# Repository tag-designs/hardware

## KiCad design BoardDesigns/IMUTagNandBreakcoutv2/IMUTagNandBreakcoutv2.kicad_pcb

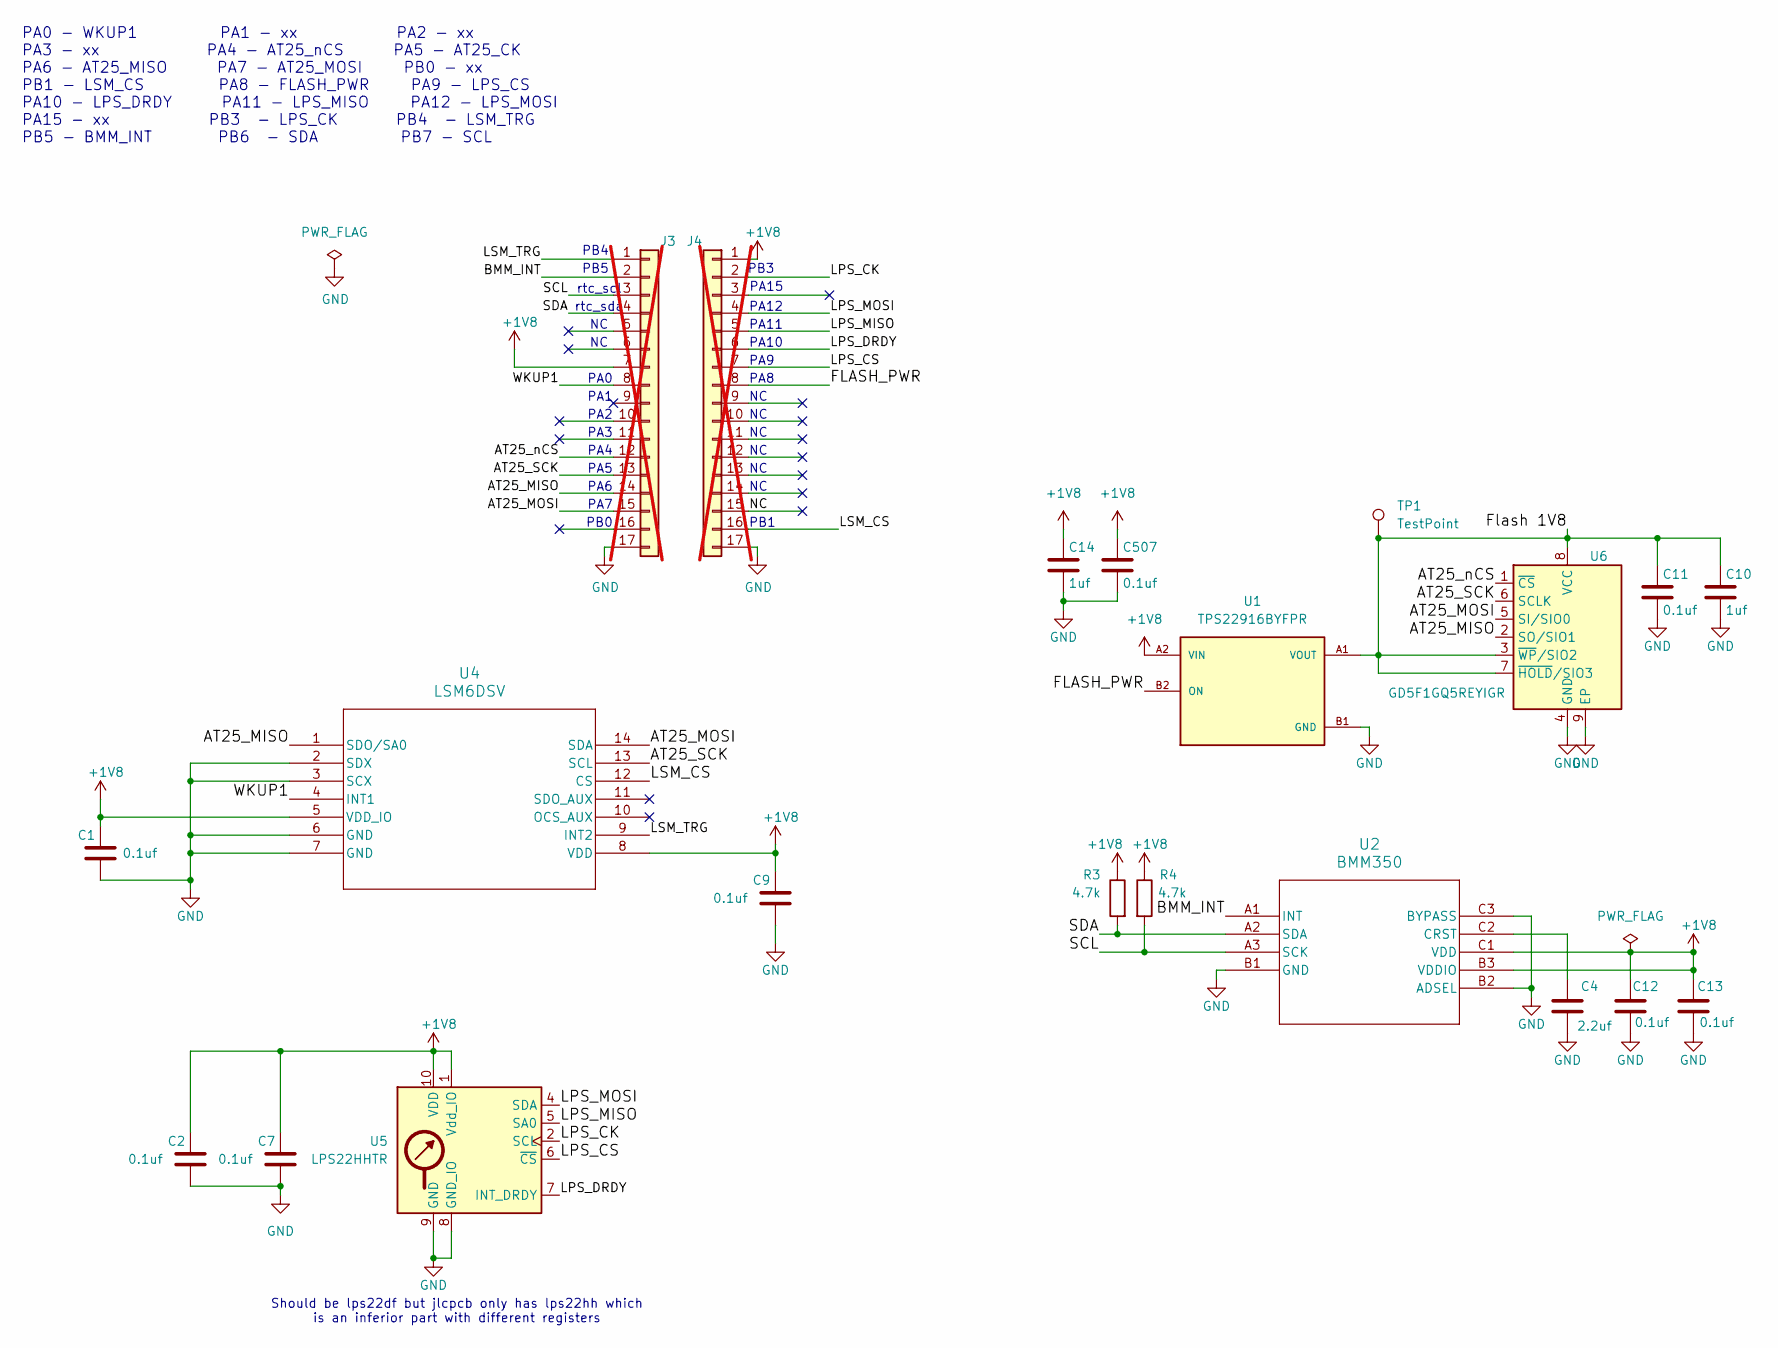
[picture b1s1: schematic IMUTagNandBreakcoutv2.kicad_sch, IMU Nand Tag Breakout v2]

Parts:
C1, C2, C7, C9, C11, C12, C13, C507: 0.1uf; C_0603_1608Metric; MPN CC0603KRX7R9BB104; LCSC C14663
C4: 2.2uf; C_0603_1608Metric; MPN GRM188R61H225KE11D; LCSC C162273
C10, C14: 1uf; C_0603_1608Metric; MPN CL10A105KB8NNNC; LCSC C15849
J3, J4: Conn_01x17; PinHeader_1x17_P2.54mm_Vertical_Staggered; not fitted
R3, R4: 4.7k; R_0603_1608Metric; MPN 0603WAF4701T5E; LCSC C23162
TP1: TestPoint; TestPoint_Pad_D2.0mm
U1: TPS22916BYFPR; IC_TPS22916BYFPR; PARTREV F; LCSC C2150095
U2: BMM350; BGA9_BMM350_BOS; MPN BMM350; LCSC C17225907
U4: LSM6DSV; LGA14-L_2P59X3P1X0P5_STM; MPN LSM6DSV; LCSC C5267399
U5: LPS22HHTR; ST_HLGA-10_2x2mm_P0.5mm_LayoutBorder3x2y; MPN LPS22HHTR; LCSC C2827824
U6: GD5F1GQ5REYIGR; WSON-8-1EP_8x6mm_P1.27mm_EP3.4x4.3mm; MPN GD5F1GQ5REYIGR; LCSC C2927042

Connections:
+1V8: C1.1, C2.1, C7.1, C9.1, C12.1, C13.1, C14.1, C507.1, J3.7, J4.1, R3.1, R4.1, U1.A2 (VIN), U2.B3 (VDDIO), U2.C1 (VDD), U4.5 (VDD_IO), U4.8 (VDD), U5.1 (Vdd_IO), U5.10 (VDD)
/AT25_MISO: J3.14, U4.1 (SDO/SA0), U6.2 (SO/SIO1)
/AT25_MOSI: J3.15, U4.14 (SDA), U6.5 (SI/SIO0)
/AT25_SCK: J3.13, U4.13 (SCL), U6.6 (SCLK)
/AT25_nCS: J3.12, U6.1 (~CS)
/BMM_INT: J3.2, U2.A1 (INT)
/FLASH_PWR: J4.8, U1.B2 (ON)
/Flash 1V8: C10.1, C11.1, TP1.1 (1_1), U1.A1 (VOUT), U6.3 (~WP/SIO2), U6.7 (~HOLD/SIO3), U6.8 (VCC)
/LPS_CK: J4.2, U5.2 (SCL)
/LPS_CS: J4.7, U5.6 (~CS)
/LPS_DRDY: J4.6, U5.7 (INT_DRDY)
/LPS_MISO: J4.5, U5.5 (SA0)
/LPS_MOSI: J4.4, U5.4 (SDA)
/LSM_CS: J4.16, U4.12 (CS)
/LSM_TRG: J3.1, U4.9 (INT2)
/NC: J4.15
/SCL: J3.3, R4.2, U2.A3 (SCK)
/SDA: J3.4, R3.2, U2.A2 (SDA)
/WKUP1: J3.8, U4.4 (INT1)
GND: C1.2, C2.2, C4.2, C7.2, C9.2, C10.2, C11.2, C12.2, C13.2, C14.2, C507.2, J3.17, J4.17, U1.B1 (GND), U2.B1 (GND), U2.B2 (ADSEL), U2.C3 (BYPASS), U4.2 (SDX), U4.3 (SCX), U4.6 (GND), U4.7 (GND), U5.3 (GND), U5.8 (GND_IO), U5.9 (GND), U6.4 (GND), U6.9 (EP)
unnamed: C4.1, U2.C2 (CRST)

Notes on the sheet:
PA1
PA9
PA2
PA0
PA8
PA7
PA15
PA5
PA4
PB3
PA6
Should be lps22df but jlcpcb only has lps22hh which is an inferior part with different registers
PA3
PA0 - WKUP1 PA1 - xx PA2 - xx PA3 - xx PA4 - AT25_nCS PA5 - AT25_CK PA6 - AT25_MISO PA7 - AT25_MOSI PB0 - xx PB1 - LSM_CS PA8 - FLASH_PWR PA9 - LPS_CS PA10 - LPS_DRDY PA11 - LPS_MISO PA12 - LPS_MOSI PA15 - xx PB3 - LPS_CK PB4 - LSM_TRG PB5 - BMM_INT PB6 - SDA PB7 - SCL
PB4
PA12
PB0
PB5
PA10
rtc_sda
PA11
PB1
rtc_scl

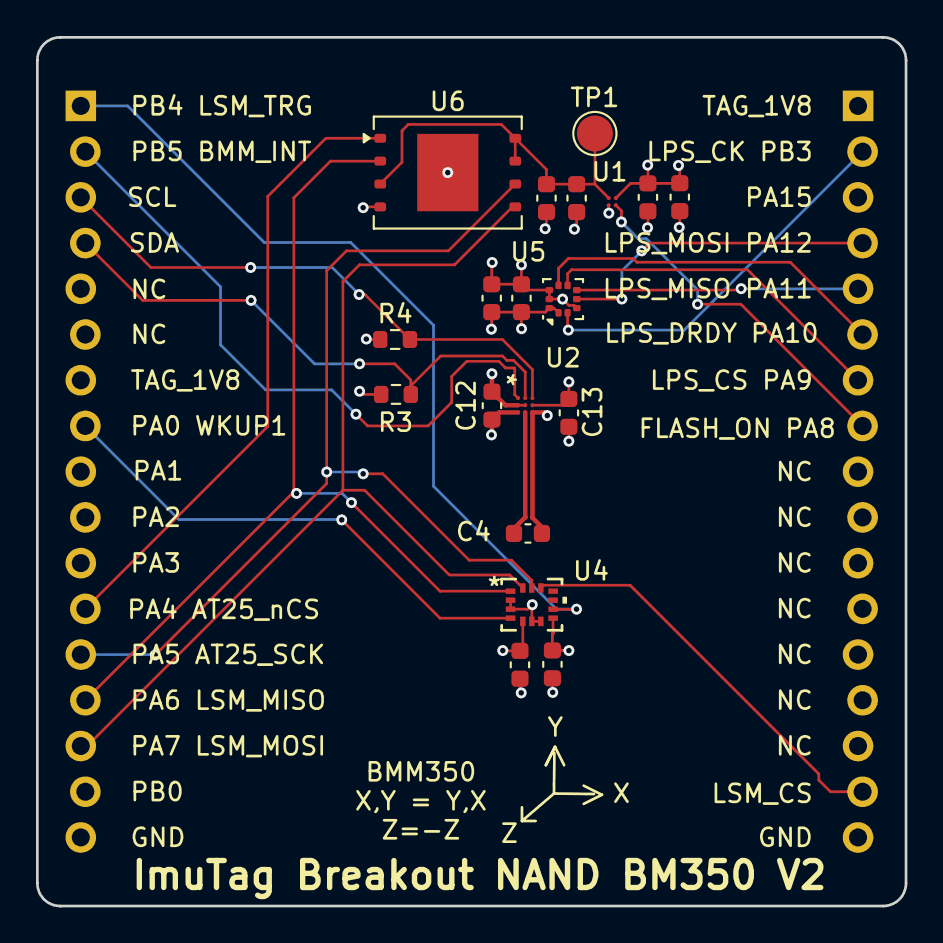
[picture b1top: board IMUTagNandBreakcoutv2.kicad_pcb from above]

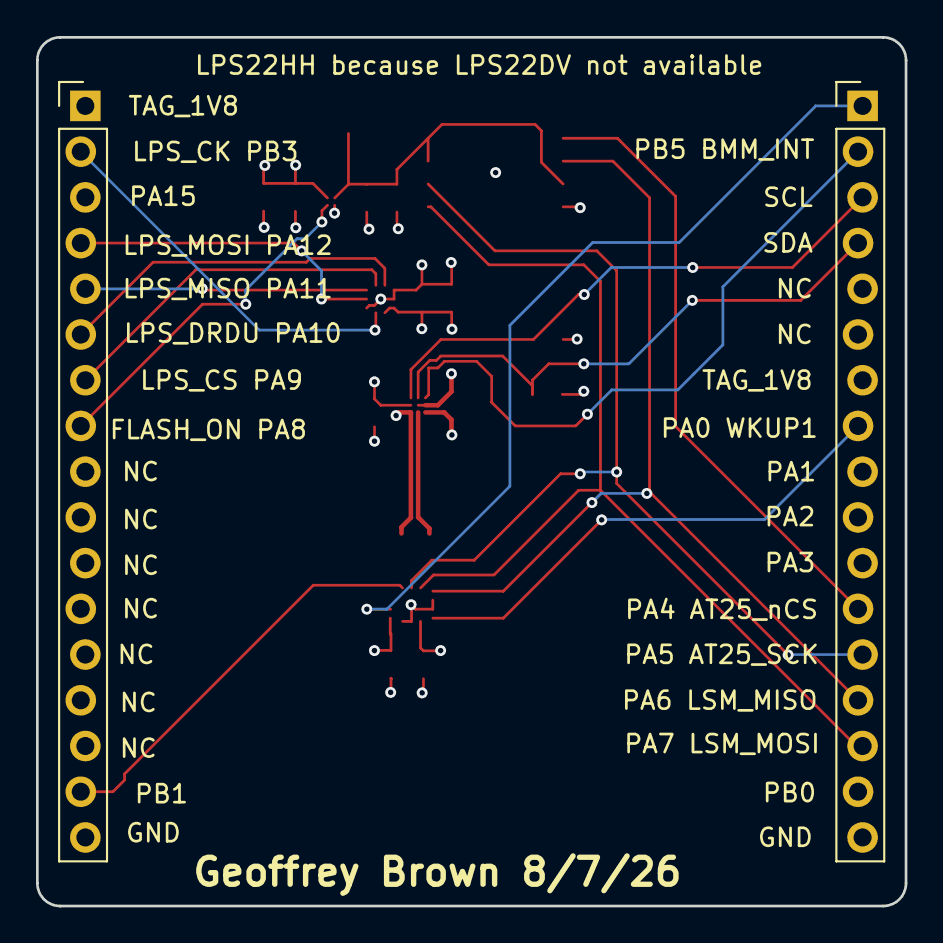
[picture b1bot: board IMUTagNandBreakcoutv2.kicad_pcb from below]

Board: 4 copper layers, 48.3 x 48.3 mm, 21 parts (2 on the bottom side), 20 nets.

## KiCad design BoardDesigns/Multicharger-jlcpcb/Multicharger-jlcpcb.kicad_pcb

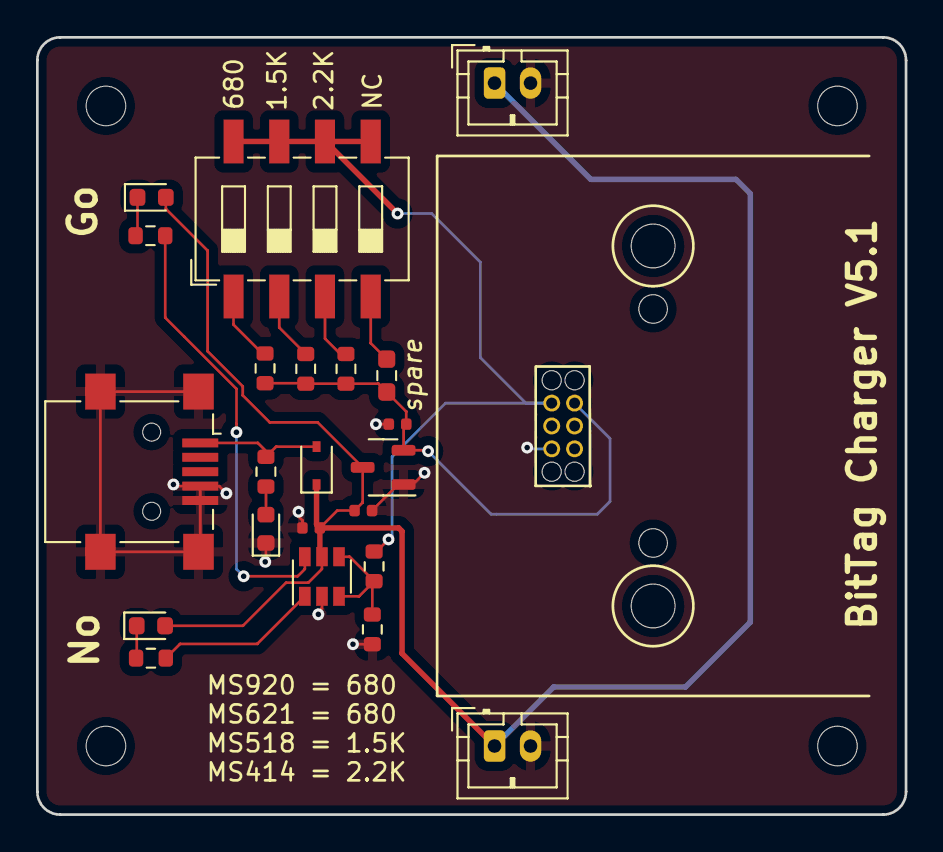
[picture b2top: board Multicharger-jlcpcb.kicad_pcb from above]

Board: 2 copper layers, 48.3 x 43.2 mm, 27 parts (0 on the bottom side), 15 nets.

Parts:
C101: 0.1uF; C_0402_1005Metric
C106: 1uF; C_0402_1005Metric
C107: 2.2uF; C_0402_1005Metric
D101: No Go Red; LED_0603_1608Metric
D102: BLUE; LED_0603_1608Metric
D103: Go Green; LED_0603_1608Metric
D104: D_Schottky; D_SOD-323
J101, J102: Conn_01x02; JST_PH_B2B-PH-K_1x02_P2.00mm_Vertical
J103: Tagbase; 6pin_tagpoints_new_offset
J104: USB_B_Mini; USB_Mini-B_Lumberg_2486_01_Horizontal
MK101, MK102, MK103, MK104: Mounting_Hole; MountingHole_2.2mm_M2
R1: 680; R_0603_1608Metric
R2: spare; R_0603_1608Metric_Pad0.98x0.95mm_HandSolder
R101: 330; R_0603_1608Metric
R102, R105: 220; R_0603_1608Metric
R103: 91K; R_0603_1608Metric
R104: 13K; R_0603_1608Metric
R106: 1500; R_0603_1608Metric
R107: 2.2K; R_0603_1608Metric
SW101: SW_DIP_x04; SW_DIP_SPSTx04_Slide_6.7x11.72mm_W8.61mm_P2.54mm_LowProfile
U101: TPS3700; SOT-23-6
U106: AP7370; SOT-23-3

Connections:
+3V3: C107.1, J103.5, R1.2, R2.1, R106.2, R107.2, U106.2 (VO)
/VIN: C101.1, C106.1, D101.2 (A), D103.2 (A), D104.1 (K), J101.1, J102.1, U101.5 (VDD), U106.3 (VI)
/Vsense: R103.2, R104.1, U101.3 (INA+), U101.4 (INB-)
GND: C101.2, C106.2, C107.2, D102.1 (K), J101.2, J102.2, J103.2, J104.4 (ID), J104.5 (GND), J104.6 (Shield), R104.2, U101.2 (GND), U106.1 (GND)
unnamed: D101.1 (K), R101.2
unnamed: D102.2 (A), R102.2
unnamed: D103.1 (K), R105.2
unnamed: D104.2 (A), J104.1 (VBUS), R102.1
unnamed: R1.1, SW101.1
unnamed: R2.2, SW101.4
unnamed: R101.1, U101.1 (OUTA)
unnamed: R105.1, U101.6 (OUTB)
unnamed: R106.1, SW101.2
unnamed: R107.1, SW101.3
TAG_VBAT: J103.6, R103.1, SW101.5, SW101.6, SW101.7, SW101.8

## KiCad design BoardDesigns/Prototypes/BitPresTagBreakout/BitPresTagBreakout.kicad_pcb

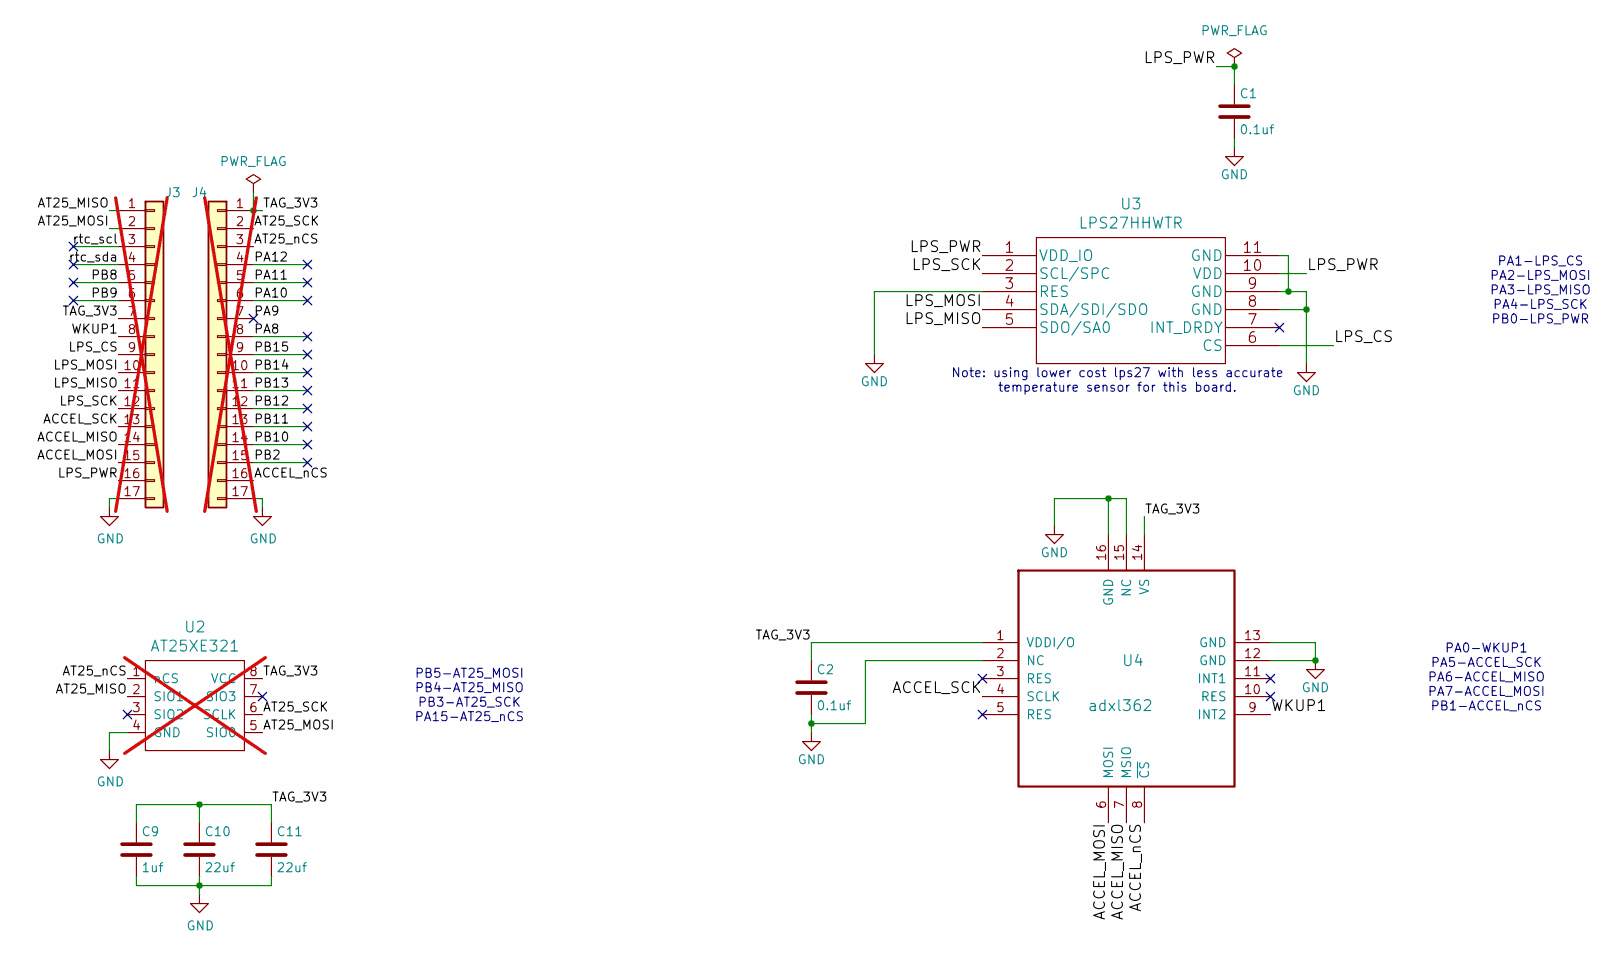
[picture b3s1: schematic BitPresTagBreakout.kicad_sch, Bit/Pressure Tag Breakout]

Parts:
C1, C2: 0.1uf; C_0201_0603Metric; MPN GRM033C81E104KE14D; LCSC C181047
C9: 1uf; C_0201_0603Metric; MPN GRM033R60J105MEA2D; LCSC C76930
C10, C11: 22uf; C_0402_1005Metric; MPN 04026D226MAT2A; LCSC C2179118
J3, J4: Conn_01x17; PinHeader_1x17_P2.54mm_Vertical_Staggered; not fitted
U2: AT25XE321; SO-8_5.3x6.2mm_P1.27mm; MPN AT25XE321D-SSHN-T; LCSC C7455379; not fitted
U3: LPS27HHWTR; MPN LPS27HHWTR; LCSC C3010792
U4: adxl362; ADXL362; MPN ADXL362BCCZ-RL7; LCSC C192252

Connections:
/ACCEL_MISO: J3.14, U4.7 (MSIO)
/ACCEL_MOSI: J3.15, U4.6 (MOSI)
/ACCEL_SCK: J3.13, U4.4 (SCLK)
/ACCEL_nCS: J4.16, U4.8 (~CS)
/AT25_MISO: J3.1, U2.2 (SIO1)
/AT25_MOSI: J3.2, U2.5 (SIO0)
/AT25_SCK: J4.2, U2.6 (SCLK)
/AT25_nCS: J4.3, U2.1 (nCS)
/LPS_CS: J3.9, U3.6 (CS)
/LPS_MISO: J3.11, U3.5 (SDO/SA0)
/LPS_MOSI: J3.10, U3.4 (SDA/SDI/SDO)
/LPS_PWR: C1.1, J3.16, U3.1 (VDD_IO), U3.10 (VDD)
/LPS_SCK: J3.12, U3.2 (SCL/SPC)
/PA8: J4.8
/PA9: J4.7
/PA10: J4.6
/PA11: J4.5
/PA12: J4.4
/PB2: J4.15
/PB8: J3.5
/PB9: J3.6
/PB10: J4.14
/PB11: J4.13
/PB12: J4.12
/PB13: J4.11
/PB14: J4.10
/PB15: J4.9
/TAG_3V3: C2.1, C9.1, C10.1, C11.1, J3.7, J4.1, U2.8 (VCC), U4.1 (VDDI/O), U4.14 (VS)
/WKUP1: J3.8, U4.9 (INT2)
/rtc_scl: J3.3
/rtc_sda: J3.4
GND: C1.2, C2.2, C9.2, C10.2, C11.2, J3.17, J4.17, U2.4 (GND), U3.3 (RES), U3.8 (GND), U3.9 (GND), U3.11 (GND), U4.2 (NC), U4.12 (GND), U4.13 (GND), U4.15 (NC), U4.16 (GND)

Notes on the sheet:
Note: using lower cost lps27 with less accurate temperature sensor for this board.
PA0-WKUP1 PA5-ACCEL_SCK PA6-ACCEL_MISO PA7-ACCEL_MOSI PB1-ACCEL_nCS
PA1-LPS_CS PA2-LPS_MOSI PA3-LPS_MISO PA4-LPS_SCK PB0-LPS_PWR
PB5-AT25_MOSI PB4-AT25_MISO PB3-AT25_SCK PA15-AT25_nCS

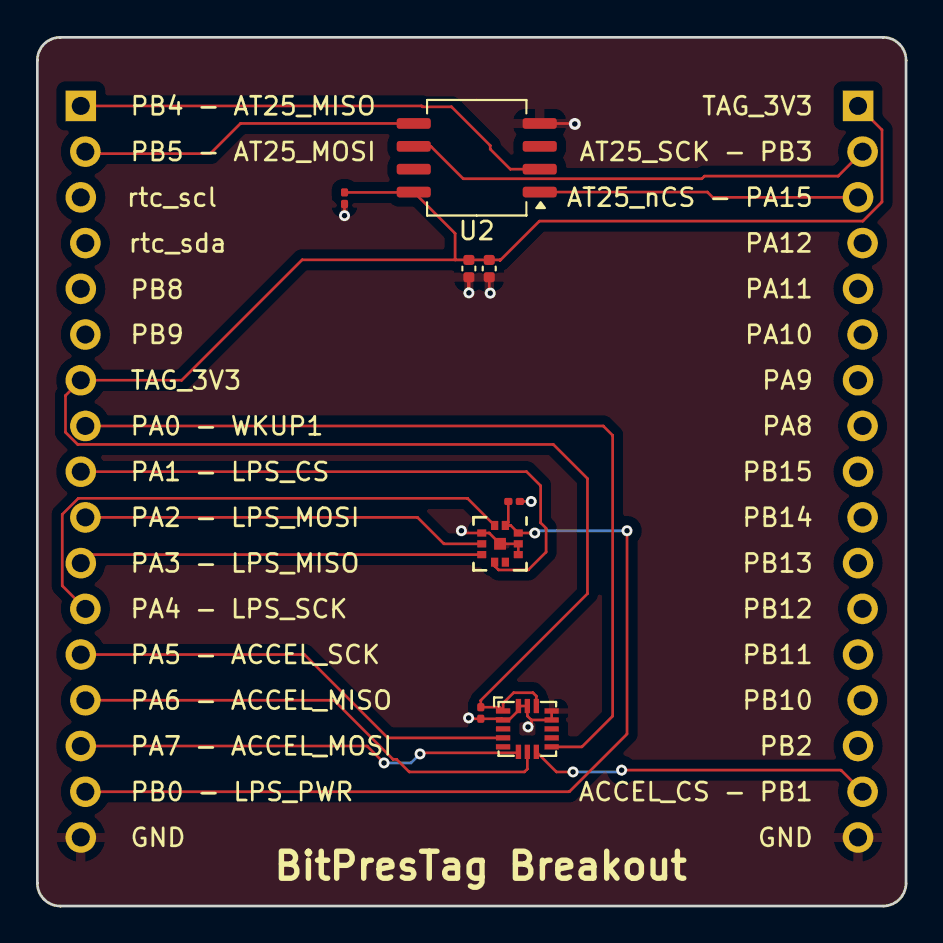
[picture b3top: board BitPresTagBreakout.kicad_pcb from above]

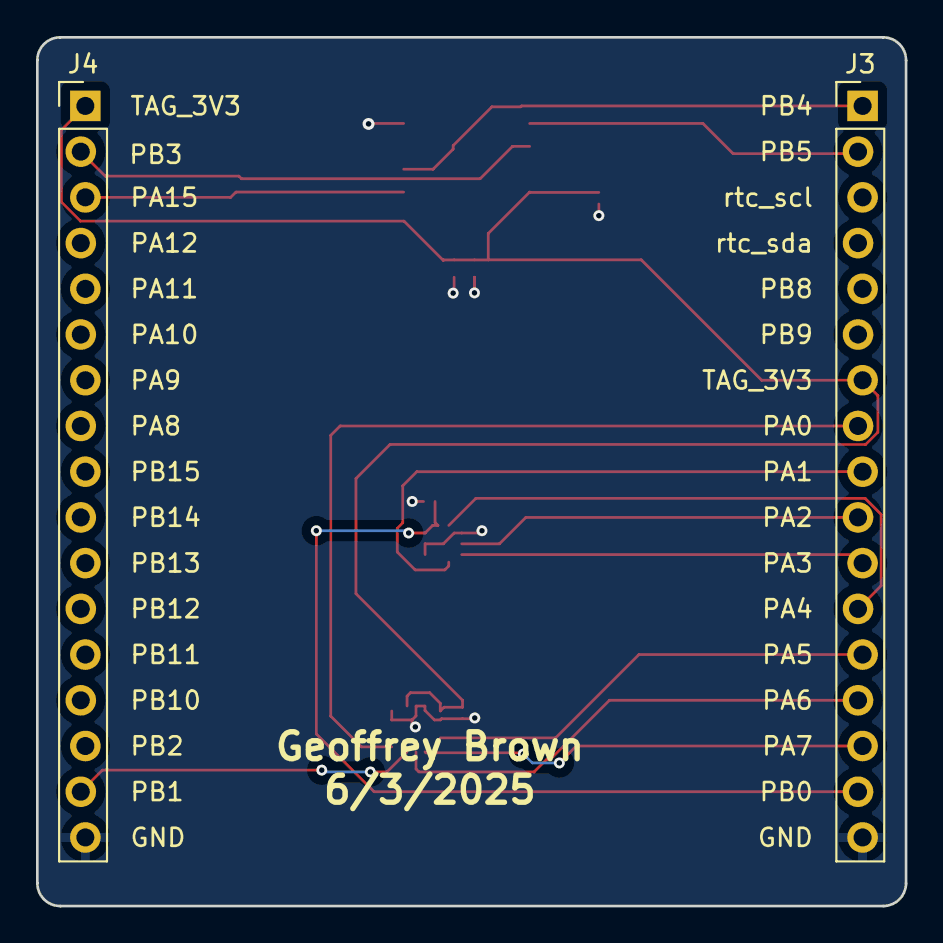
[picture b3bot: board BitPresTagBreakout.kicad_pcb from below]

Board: 2 copper layers, 48.3 x 48.3 mm, 10 parts (2 on the bottom side), 16 nets.

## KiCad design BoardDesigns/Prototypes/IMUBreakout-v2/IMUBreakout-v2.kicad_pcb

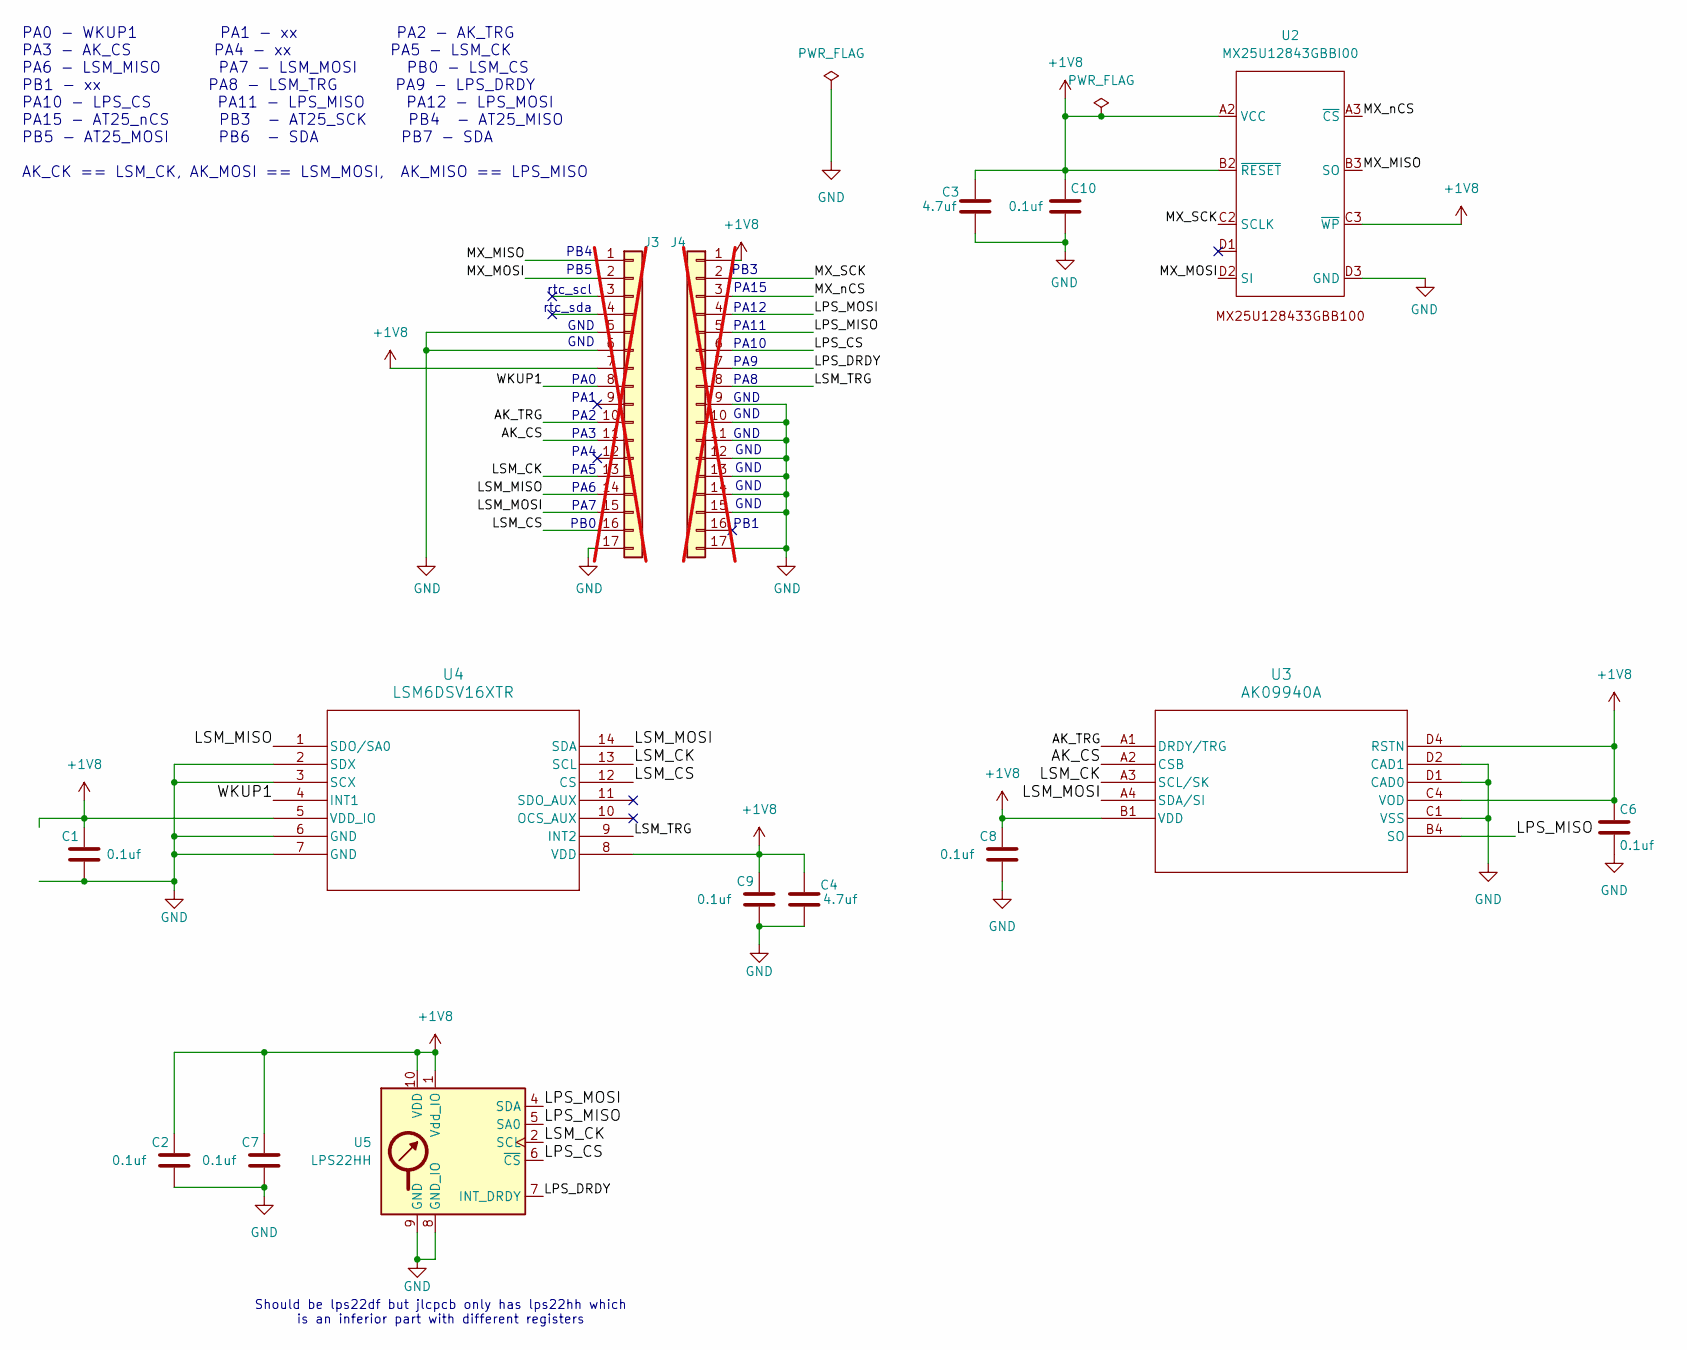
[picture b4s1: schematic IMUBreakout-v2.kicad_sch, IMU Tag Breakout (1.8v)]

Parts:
C1, C2, C6, C7, C8, C9, C10: 0.1uf; C_0603_1608Metric; MPN CC0603KRX7R9BB104; LCSC C14663
C3, C4: 4.7uf; C_0603_1608Metric; MPN CL10A475KO8NNNC; LCSC C19666
J3, J4: Conn_01x17; PinHeader_1x17_P2.54mm_Vertical_Staggered; not fitted
U2: MX25U12843GBBI00; IC_MX25U12843GBBI00; MPN MX25U12843GBBI00; LCSC C7316586
U3: AK09940A; AK09940a; MPN AK09940A; LCSC C6794828
U4: LSM6DSV16XTR; LGA-14_3x2.5mm_P0.5mm_LayoutBorder3x4y; MPN LSM6DSV; LCSC C5267406
U5: LPS22HH; ST_HLGA-10_2x2mm_P0.5mm_LayoutBorder3x2y; MPN LPS22HH; LCSC C2827824

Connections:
+1V8: C1.1, C2.1, C3.1, C4.1, C6.1, C7.1, C8.1, C9.1, C10.1, J3.7, J4.1, U2.A2 (VCC), U2.B2 (~RESET), U2.C3 (~WP), U3.B1 (VDD), U3.C4 (VOD), U3.D4 (RSTN), U4.5 (VDD_IO), U4.8 (VDD), U5.1 (Vdd_IO), U5.10 (VDD)
/AK_CS: J3.11, U3.A2 (CSB)
/AK_TRG: J3.10, U3.A1 (DRDY/TRG)
/LPS_CS: J4.6, U5.6 (~CS)
/LPS_DRDY: J4.7, U5.7 (INT_DRDY)
/LPS_MISO: J4.5, U3.B4 (SO), U5.5 (SA0)
/LPS_MOSI: J4.4, U5.4 (SDA)
/LSM_CK: J3.13, U3.A3 (SCL/SK), U4.13 (SCL), U5.2 (SCL)
/LSM_CS: J3.16, U4.12 (CS)
/LSM_MISO: J3.14, U4.1 (SDO/SA0)
/LSM_MOSI: J3.15, U3.A4 (SDA/SI), U4.14 (SDA)
/LSM_TRG: J4.8, U4.9 (INT2)
/MX_MISO: J3.1, U2.B3 (SO)
/MX_MOSI: J3.2, U2.D2 (SI)
/MX_SCK: J4.2, U2.C2 (SCLK)
/MX_nCS: J4.3, U2.A3 (~CS)
/WKUP1: J3.8, U4.4 (INT1)
GND: C1.2, C2.2, C3.2, C4.2, C6.2, C7.2, C8.2, C9.2, C10.2, J3.5, J3.6, J3.17, J4.9, J4.10, J4.11, J4.12, J4.13, J4.14, J4.15, J4.17, U2.D3 (GND), U3.C1 (VSS), U3.D1 (CAD0), U3.D2 (CAD1), U4.2 (SDX), U4.3 (SCX), U4.6 (GND), U4.7 (GND), U5.3 (GND), U5.8 (GND_IO), U5.9 (GND)

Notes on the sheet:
PA1
PA9
PA2
PA0
PA8
PA7
PA15
PA5
GND
PA4
PB3
PA6
Should be lps22df but jlcpcb only has lps22hh which is an inferior part with different registers
PA3
PB4
PA12
PB0
PA0 - WKUP1 PA1 - xx PA2 - AK_TRG PA3 - AK_CS PA4 - xx PA5 - LSM_CK PA6 - LSM_MISO PA7 - LSM_MOSI PB0 - LSM_CS PB1 - xx PA8 - LSM_TRG PA9 - LPS_DRDY PA10 - LPS_CS PA11 - LPS_MISO PA12 - LPS_MOSI PA15 - AT25_nCS PB3 - AT25_SCK PB4 - AT25_MISO PB5 - AT25_MOSI PB6 - SDA PB7 - SDA AK_CK == LSM_CK, AK_M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
PB5
PA10
rtc_sda
PA11
PB1
rtc_scl

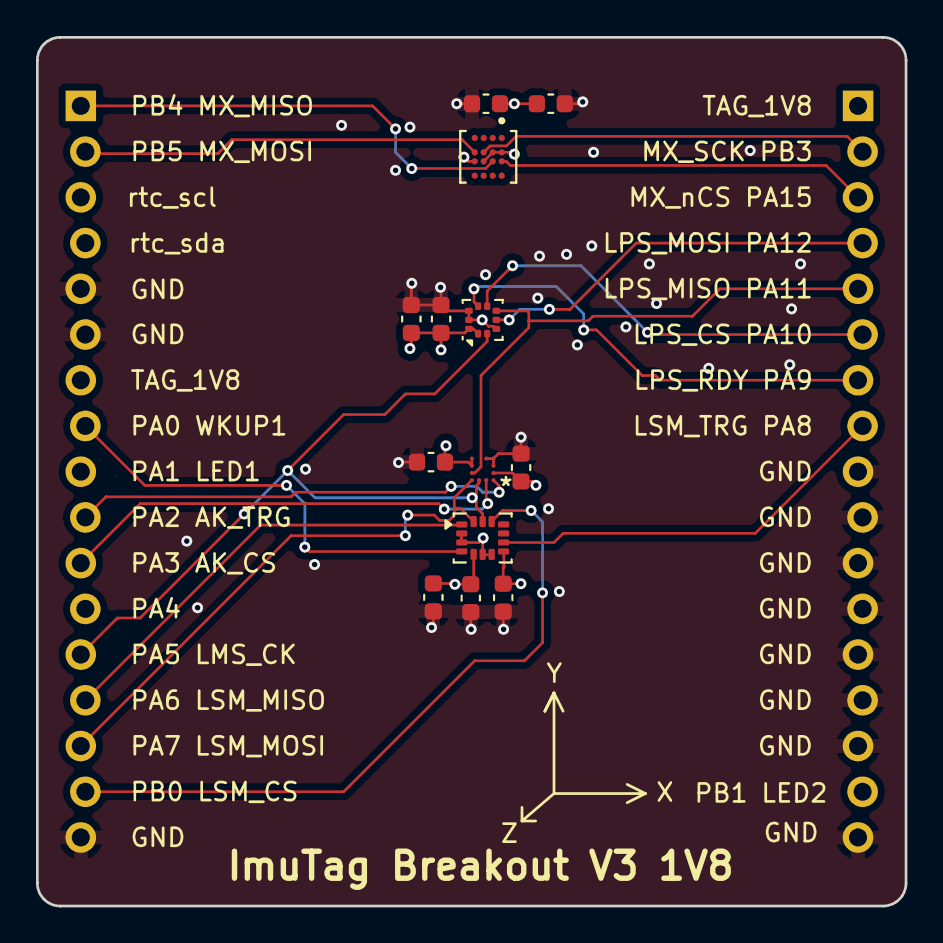
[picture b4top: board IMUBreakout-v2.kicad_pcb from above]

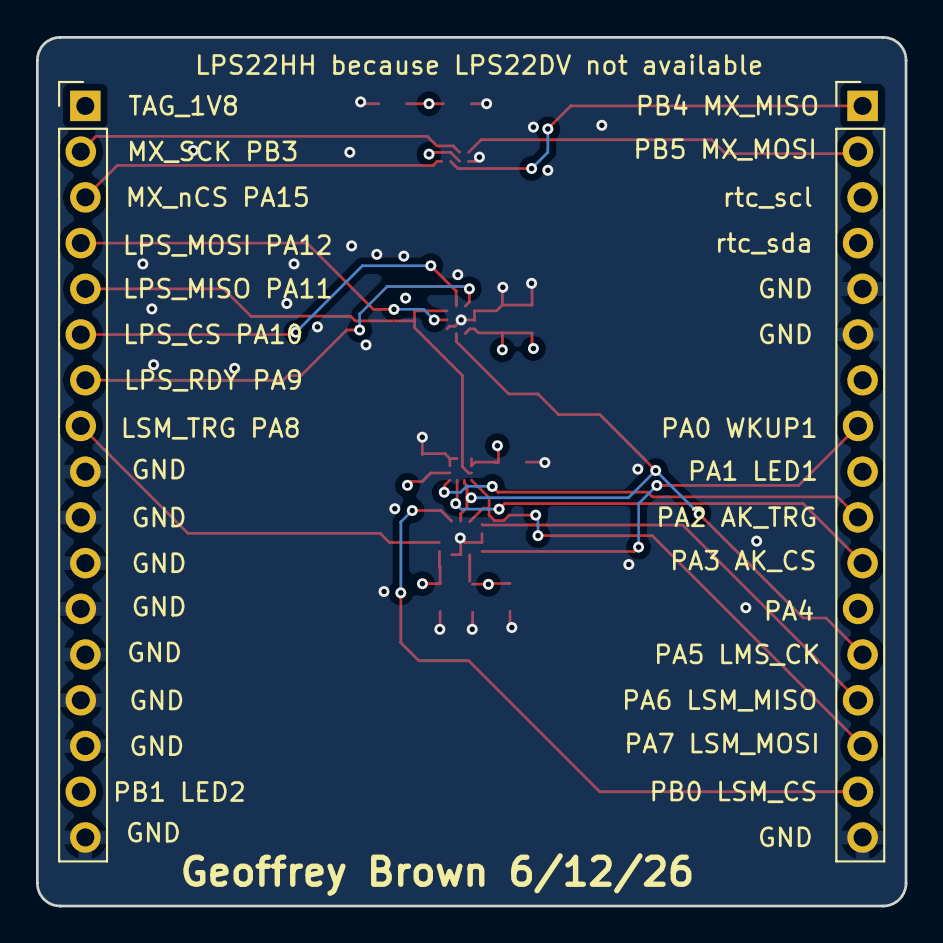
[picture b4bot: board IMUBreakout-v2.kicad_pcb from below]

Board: 4 copper layers, 48.3 x 48.3 mm, 15 parts (2 on the bottom side), 18 nets.

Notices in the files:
parts and their libraries:
Copyright 2016 Accelerated Designs. All rights reserved.
